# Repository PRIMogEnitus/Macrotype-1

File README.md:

# Macrotype-1
 Macropad for work(maybe?)

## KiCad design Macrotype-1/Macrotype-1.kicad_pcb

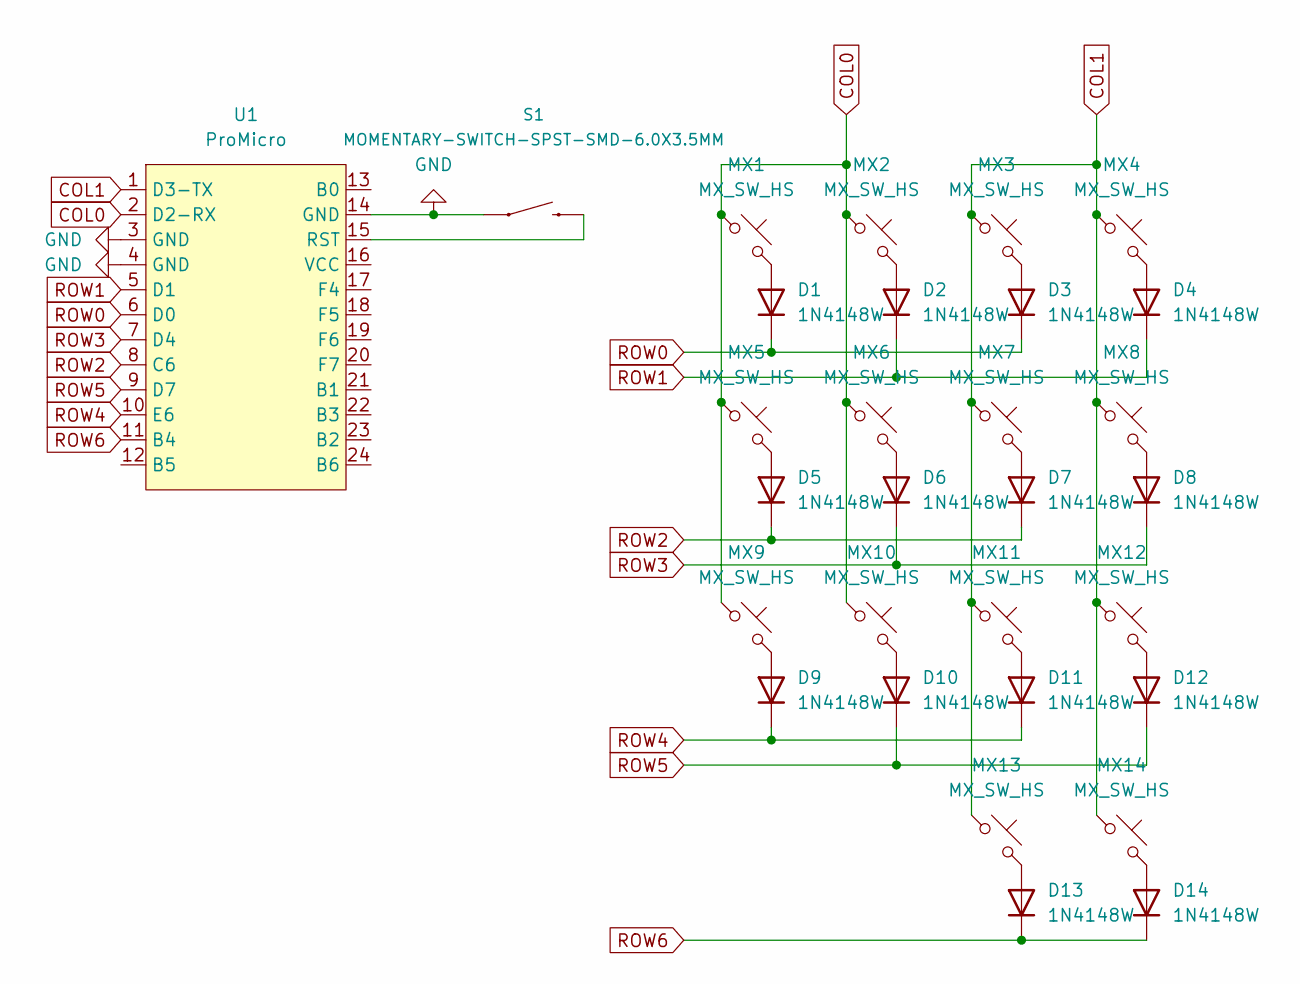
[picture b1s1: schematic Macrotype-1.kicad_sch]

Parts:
D1, D2, D3, D4, D5, D6, D7, D8, D9, D10, D11, D12, D13, D14: 1N4148W; D_SOD-123
MX1, MX2, MX3, MX4, MX5, MX6, MX7, MX8, MX9, MX10, MX11, MX12, MX13, MX14: MX_SW_HS; SW_MX_HS_1u
S1: MOMENTARY-SWITCH-SPST-SMD-6.0X3.5MM; TACTILE_SWITCH_SMD_6.0X3.5MM
U1: ProMicro; ProMicro_USBup

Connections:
COL0: MX1.1, MX2.1, MX5.1, MX6.1, MX9.1, MX10.1, U1.2 (D2-RX)
COL1: MX3.1, MX4.1, MX7.1, MX8.1, MX11.1, MX12.1, MX13.1, MX14.1, U1.1 (D3-TX)
GND: S1.1, U1.3 (GND), U1.4 (GND), U1.14 (GND)
unnamed: D1.2 (A), MX1.2
unnamed: D2.2 (A), MX2.2
unnamed: D3.2 (A), MX3.2
unnamed: D4.2 (A), MX4.2
unnamed: D5.2 (A), MX5.2
unnamed: D6.2 (A), MX6.2
unnamed: D7.2 (A), MX7.2
unnamed: D8.2 (A), MX8.2
unnamed: D9.2 (A), MX9.2
unnamed: D10.2 (A), MX10.2
unnamed: D11.2 (A), MX11.2
unnamed: D12.2 (A), MX12.2
unnamed: D13.2 (A), MX13.2
unnamed: D14.2 (A), MX14.2
unnamed: S1.2, U1.15 (RST)
ROW0: D1.1 (K), D3.1 (K), U1.6 (D0)
ROW1: D2.1 (K), D4.1 (K), U1.5 (D1)
ROW2: D5.1 (K), D7.1 (K), U1.8 (C6)
ROW3: D6.1 (K), D8.1 (K), U1.7 (D4)
ROW4: D9.1 (K), D11.1 (K), U1.10 (E6)
ROW5: D10.1 (K), D12.1 (K), U1.9 (D7)
ROW6: D13.1 (K), D14.1 (K), U1.11 (B4)

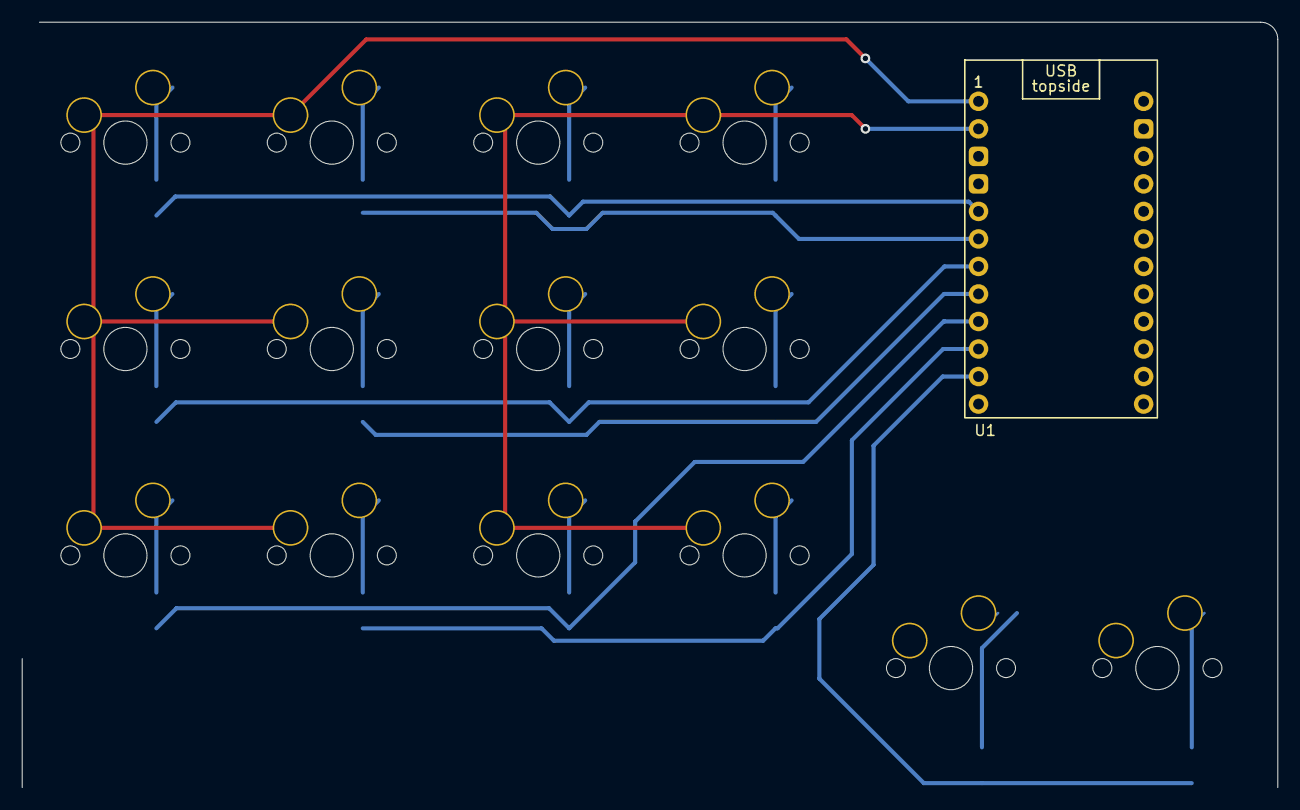
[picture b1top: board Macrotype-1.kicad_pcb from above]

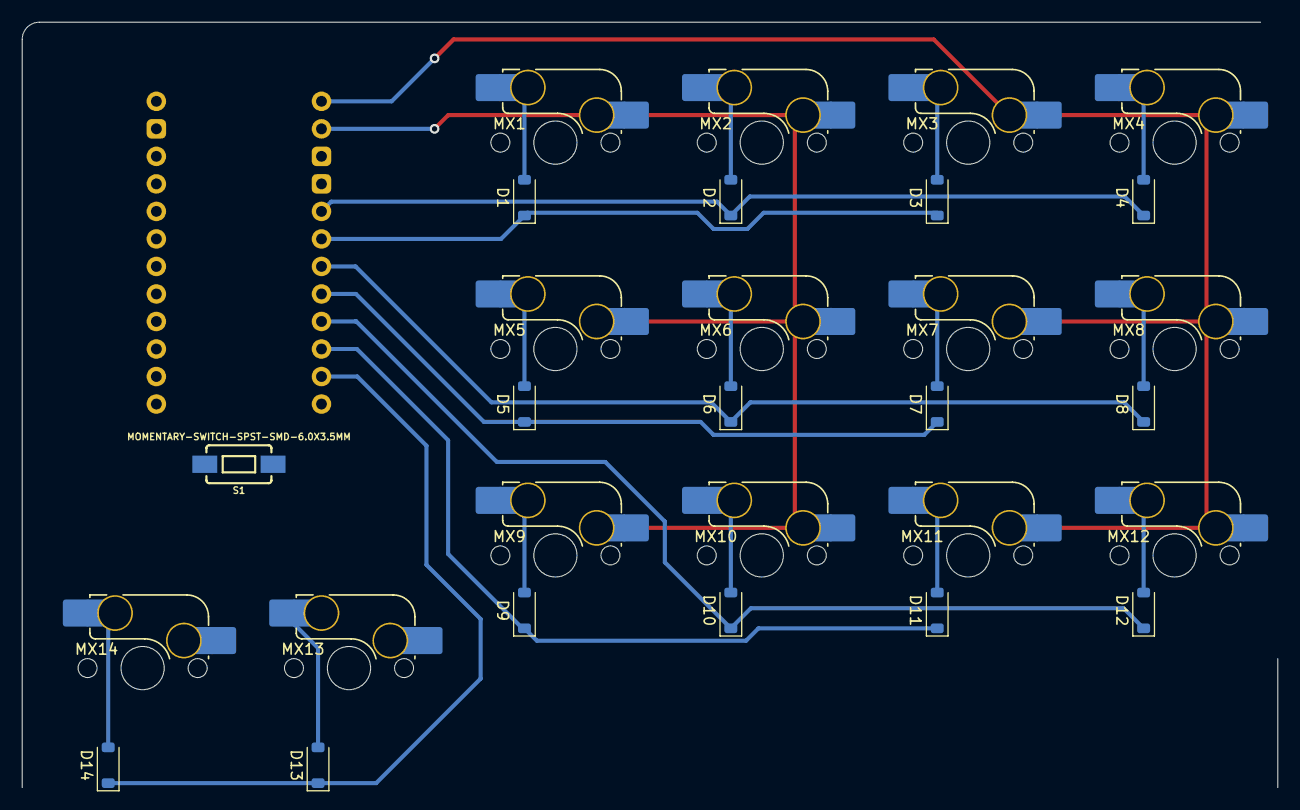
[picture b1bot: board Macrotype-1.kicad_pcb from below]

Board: 2 copper layers, 115.9 x 70.6 mm, 30 parts (29 on the bottom side), 25 nets.

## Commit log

2023-12-03 Initialization
